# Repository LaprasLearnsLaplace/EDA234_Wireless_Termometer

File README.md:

# EDA234 Wireless Temperature Monitoring System

FPGA-based indoor/outdoor temperature monitoring system developed for EDA234 Digital Project Laboratory course at Chalmers University of Technology, implemented on Nexys A7 FPGA development board using VHDL.

### Temperature Sensing
- Indoor: ADT7420 with I2C protocol 
- Outdoor: DS18B20 with 1-Wire protocol 

### Display System
- LCD Display (DMC16117A): Detailed temperature info
- OLED Display: Outdoor unit visualization  
- Seven-segment Display: Time (outdoor) and temperature (indoor)

### Data Management
- DDR2 SDRAM for data storage
- Maximum/minimum temperature tracking
- Real-time clock (DS1302) for temporal logging
- User-configurable temperature thresholds

### Interface & Control
- 4x4 matrix keyboard for settings
- Bluetooth communication (9600 baud)
- Configurable alarm system 
- FPGA onboard buttons/switches

## Hardware Requirements

- Nexys A7-100T FPGA Board
- DMC16117A LCD Module  
- DS1302 RTC Module
- HC-06 Bluetooth Module
- HS96L01W4S03 OLED Display
- 4x4 Matrix Keyboard
- DS18B20 Temperature Sensor
- ADT7420 Temperature Sensor

## Project Structure
-  Indoor unit VHDL implementation
- `outdoor/`: Outdoor unit VHDL implementation
- `Board/`: PCB board files

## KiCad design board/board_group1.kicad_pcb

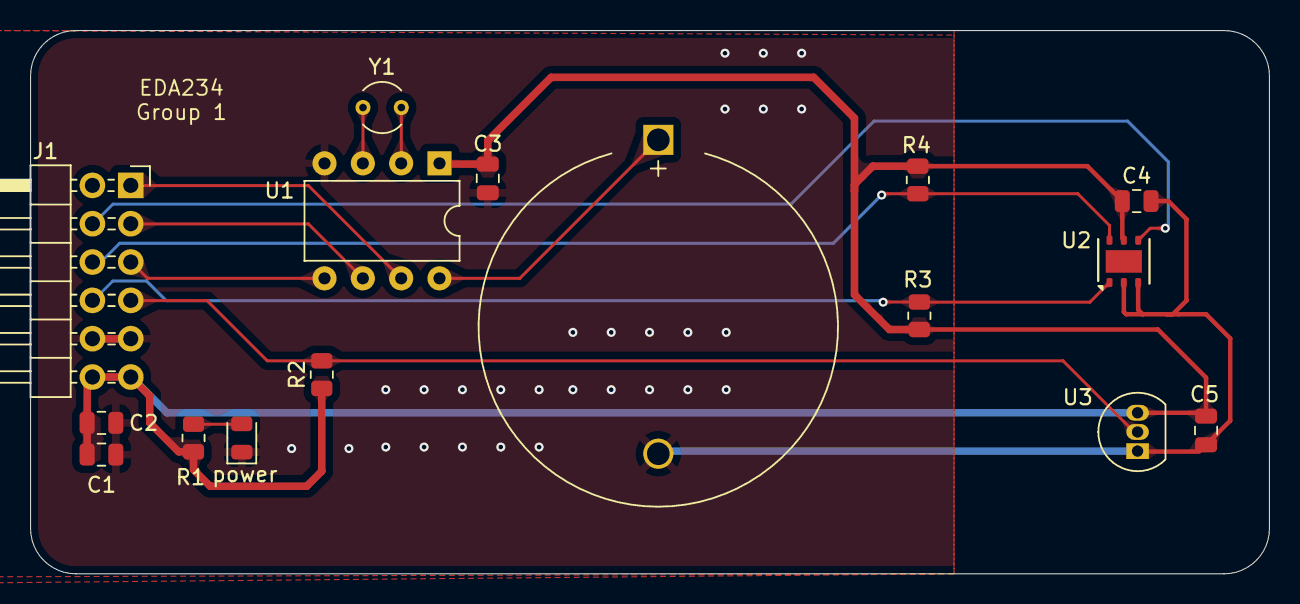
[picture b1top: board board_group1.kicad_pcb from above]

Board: 2 copper layers, 82.1 x 36.0 mm, 16 parts (0 on the bottom side), 13 nets.

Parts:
BT1: Battery_Cell; BatteryHolder_MYOUNG_BS-07-A1BJ001_CR2032
C1, C3, C4, C5: 100n; C_0805_2012Metric
C2: 10u; C_0805_2012Metric
J1: Conn_02x06_Top_Bottom; PinHeader_2x06_P2.54mm_Horizontal
R1: R; R_0805_2012Metric
R2, R3, R4: 4.7k; R_0805_2012Metric
U1: DS1302+; DIP-8_W7.62mm
U2: HDC2080; Texas_PWSON-N6
U3: DS18S20; TO-92_Inline
Y1: Crystal; Crystal_AT310_D3.0mm_L10.0mm_Vertical
power: LED; LED_0805_2012Metric

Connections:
+3.3V: C1.1, C2.1, C3.1, C4.1, C5.1, J1.6, J1.12, R1.1, R2.1, R3.1, R4.1, U1.1 (VCC2), U2.5 (VDD), U3.3 (V_{DD})
CLK_rtl: J1.1, U1.7 (SCLK)
DAT: J1.2, U1.6 (I/O)
DQ: J1.4, R2.2, U3.2 (DQ)
GND: BT1.2 (-), C1.2, C2.2, C3.2, C4.2, C5.2, J1.5, J1.11, U1.4 (GND), U2.2 (GND), U2.3 (ADDR), U3.1 (GND), power.1 (K)
INT: J1.8, U2.4 (DRDY)
unnamed: BT1.1 (+), U1.8 (VCC1)
unnamed: U1.2 (X1), Y1.2
unnamed: U1.3 (X2), Y1.1
unnamed: R1.2, power.2 (A)
RST_rtl: J1.3, U1.5 (CE)
SCL: J1.9, R4.2, U2.6 (SCL)
SDA: J1.10, R3.2, U2.1 (SDA)

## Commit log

2024-11-10 温度计构思_1110
    week1同老师沟通前_中文版
2024-11-17 add uart_ctrl.vhd, only uart_tx available now
2024-11-17 add uart_ctrl.vhd, only uart_tx available now, ziheng li
2024-11-19 update block diagram
    update block diagram
2024-11-20 Add i2c_ctrl.vhd and ADT7420.vhd
2024-12-15 add UART with FIFO depth 1024, I2C control, lcd, keyboard by Fengfeng, organized top
2024-12-15 modified wdf
2024-12-18 添加RTC模块，包括时钟分频器、十进制到BCD解码器、时间设置和DS1302控制器
2025-01-12 close to final version
2025-01-20 Updated format + comments
2025-02-06 PCB Board update
